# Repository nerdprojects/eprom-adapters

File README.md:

# EPROM Adapters

## SST39SF040 to M27C4001

This is an adapter PCB that can be used to make the "Microchip SST39SF040" pin-compatible with the M27C4001 EPROM.

An alternative to this adapter could be the "Winbond W27E040" chip, which is pin-compatible with the M27C4001.

I used it for patching ROMs in my pinball machines:
https://github.com/nerdprojects/pinball-cvsd-patcher

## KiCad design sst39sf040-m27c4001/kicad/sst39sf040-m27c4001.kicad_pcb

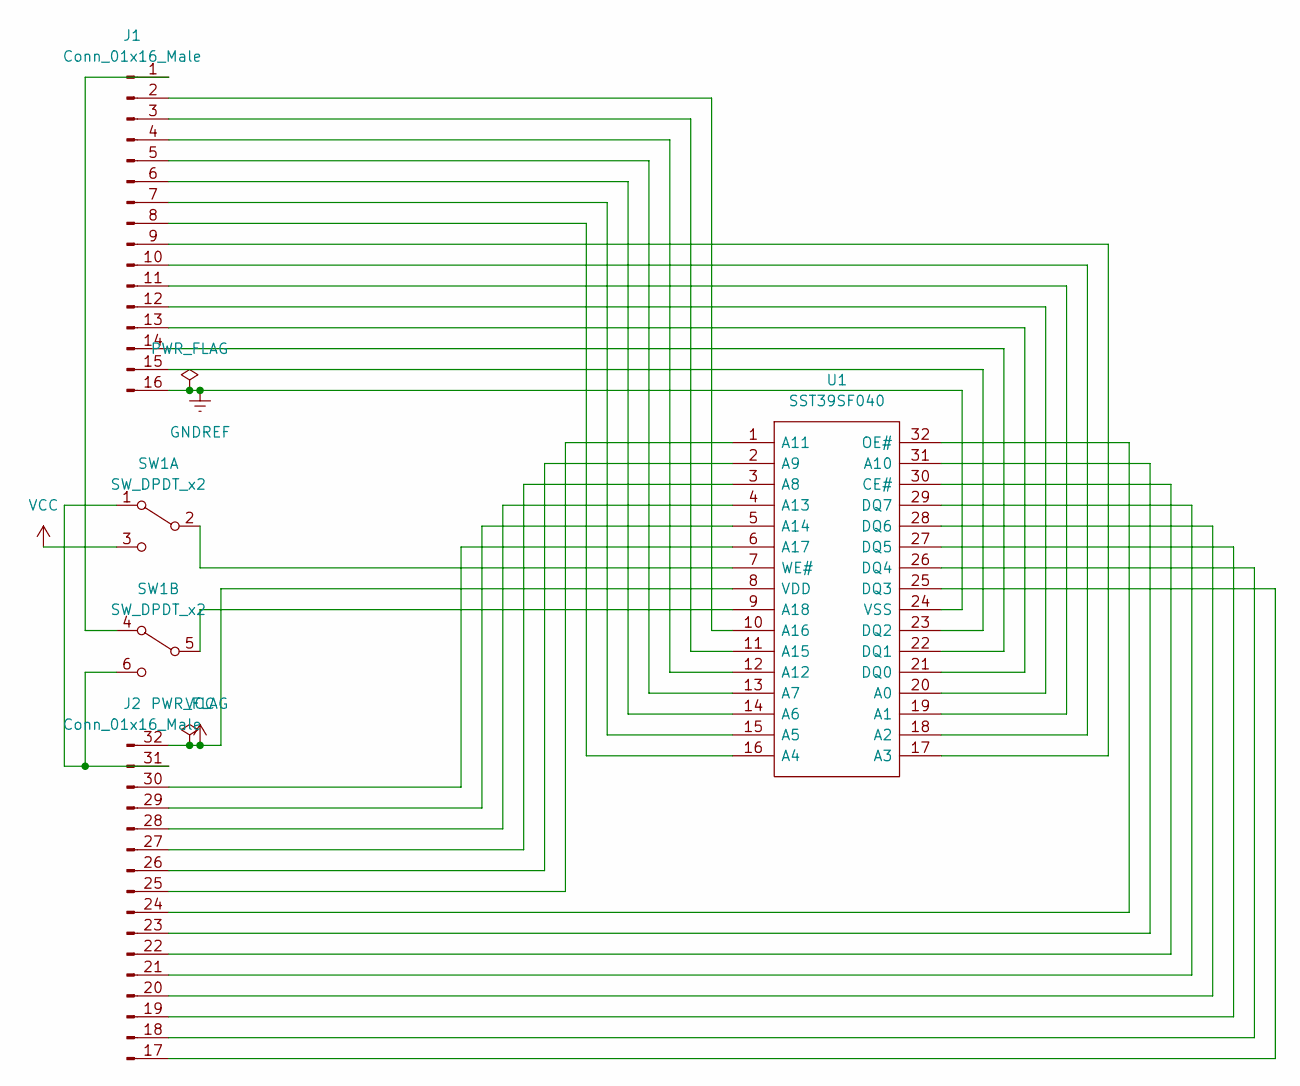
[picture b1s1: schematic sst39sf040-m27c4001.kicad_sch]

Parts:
J1, J2: Conn_01x16_Male; PinHeader_1x16_P2.54mm_Vertical
SW1: SW_DPDT_x2; JS202011SCQN
U1: SST39SF040; SOP50P1400X120-32N; Manufacturer_Part_Number SST39SF040-45-4I-WHE-T

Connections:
GNDREF: J1.16, U1.24 (VSS)
unnamed: J1.1, SW1.4 (A)
unnamed: J1.2, U1.10 (A16)
unnamed: J1.3, U1.11 (A15)
unnamed: J1.4, U1.12 (A12)
unnamed: J1.5, U1.13 (A7)
unnamed: J1.6, U1.14 (A6)
unnamed: J1.7, U1.15 (A5)
unnamed: J1.8, U1.16 (A4)
unnamed: J1.9, U1.17 (A3)
unnamed: J1.10, U1.18 (A2)
unnamed: J1.11, U1.19 (A1)
unnamed: J1.12, U1.20 (A0)
unnamed: J1.13, U1.21 (DQ0)
unnamed: J1.14, U1.22 (DQ1)
unnamed: J1.15, U1.23 (DQ2)
unnamed: J2.17, U1.25 (DQ3)
unnamed: J2.18, U1.26 (DQ4)
unnamed: J2.19, U1.27 (DQ5)
unnamed: J2.20, U1.28 (DQ6)
unnamed: J2.21, U1.29 (DQ7)
unnamed: J2.22, U1.30 (CE#)
unnamed: J2.23, U1.31 (A10)
unnamed: J2.24, U1.32 (OE#)
unnamed: J2.31, SW1.1 (A), SW1.6 (C)
unnamed: J2.25, U1.1 (A11)
unnamed: J2.26, U1.2 (A9)
unnamed: J2.27, U1.3 (A8)
unnamed: J2.28, U1.4 (A13)
unnamed: J2.29, U1.5 (A14)
unnamed: J2.30, U1.6 (A17)
unnamed: SW1.2 (B), U1.7 (WE#)
unnamed: SW1.5 (B), U1.9 (A18)
VCC: J2.32, SW1.3 (C), U1.8 (VDD)

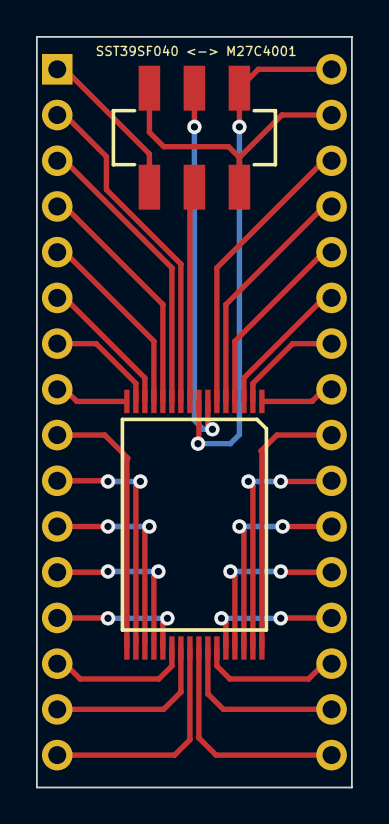
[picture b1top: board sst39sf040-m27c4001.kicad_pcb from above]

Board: 2 copper layers, 17.5 x 41.7 mm, 4 parts (0 on the bottom side), 34 nets.

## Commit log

2024-05-09 fix wrong distance of pin row
